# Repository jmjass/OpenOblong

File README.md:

# OpenRectangleCubsMod
Custom PCBs for a RP2040 powered rectangle controller.

Modified version of https://github.com/Armastardo/OpenRectangle that decreases size of the PCB and changes button layout to accomodate.

Original Dimensions: 339.13mm x 141.22mm

Modified Dimensions: 282.7mm x 136.22mm

Case Dimensions: 296mm x 154.4mm (~11.65" x ~6.08")

(Thickness of the case varies based on thickness of acrylic layers)

## Part Links:

Case Standoffs: 

https://www.aliexpress.us/item/2251832708378430.html?gatewayAdapt=glo2usa4itemAdapt&_randl_shipto=US

Calculate the thickness of your case and order standoffs about 1mm shorter than the case.

Case Screws: 
https://www.amazon.com/dp/B0798227SK?psc=1&ref=ppx_yo2ov_dt_b_product_details

Any M2 screws will work, I got these because I wanted black ones that are flush with the case.

Acrylic:

https://houstonacrylic.com/

There is a huge variety of colors and different designs of acrylic offered by these guys but they are a bit more expensive than other places. Also I had to pay about $17 for shipping so be sure to account for shipping costs in budget. If you order a 12 x 19 inch sheet from here you are able to cut 3 layers out of it.

If you are trying to make it as cheap as possible, I would recommend shopping around for clear acrylic because clear seemed to be the cheapest when I was looking. Here are a couple different thickness ones from amazon that I found:

1/8" For Top/Bottom Layers + PCB Layers on Aluminum Switchplate Design: https://www.amazon.com/dp/B09XR8NB28?psc=1&ref=ppx_yo2ov_dt_b_product_details

Acrylic Switchplate (.06"): https://www.amazon.com/dp/B09LTYDYKP?psc=1&ref=ppx_yo2ov_dt_b_product_details

PCB Layer/Hotswap Cutout Layer on Acylic Switchplate Design (.08"): https://www.amazon.com/dp/B09N3PN8PG?ref=ppx_yo2ov_dt_b_product_details&th=1

I recommend doing some searching on your own as there may be different options that are cheaper. 8" x 12" works the best for cutting 1 panel per sheet and for getting mroe than 1 panel per sheet you need multiples of 6.315" x 12". For example, 12" x 19" can get you 3 layers with very little margin of error or 12" x 21" would get you 3 layers way more comfortable although you are unlikely to find this size and would more commonly find 12" x 24"

3.5mm M1.6 PCB Standoffs:

https://www.ebay.com/itm/185215966272?var=692974532230

3mm M1.6 PCB Screws:

https://www.ebay.com/itm/183908369734

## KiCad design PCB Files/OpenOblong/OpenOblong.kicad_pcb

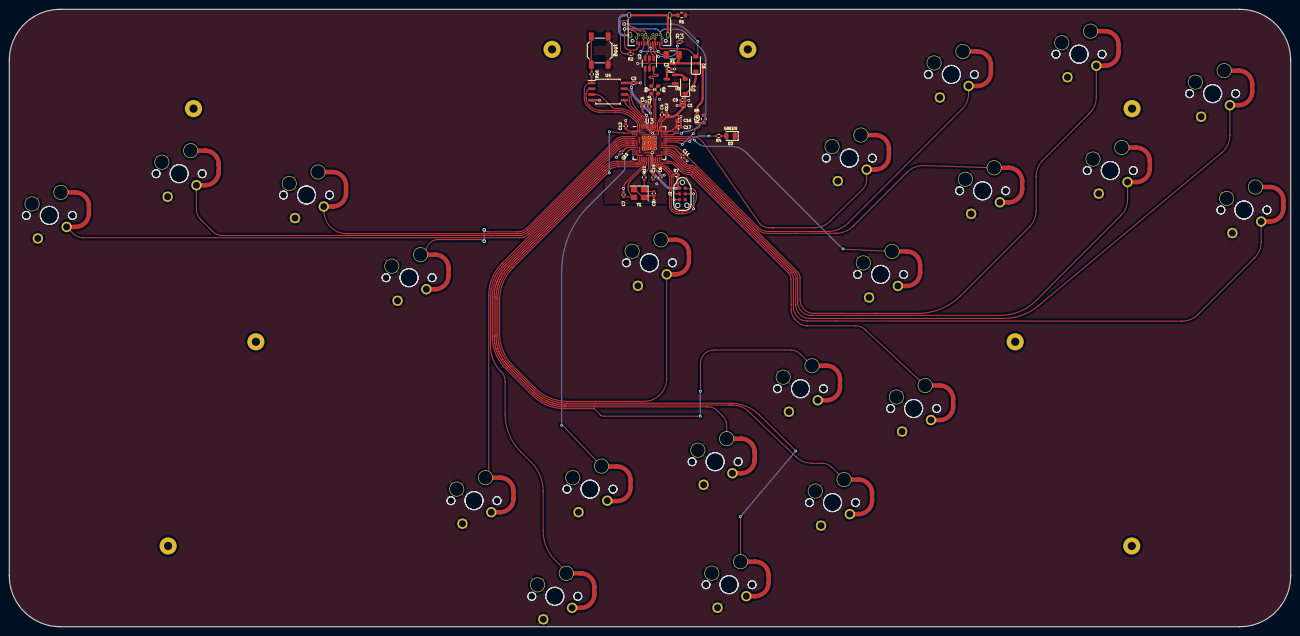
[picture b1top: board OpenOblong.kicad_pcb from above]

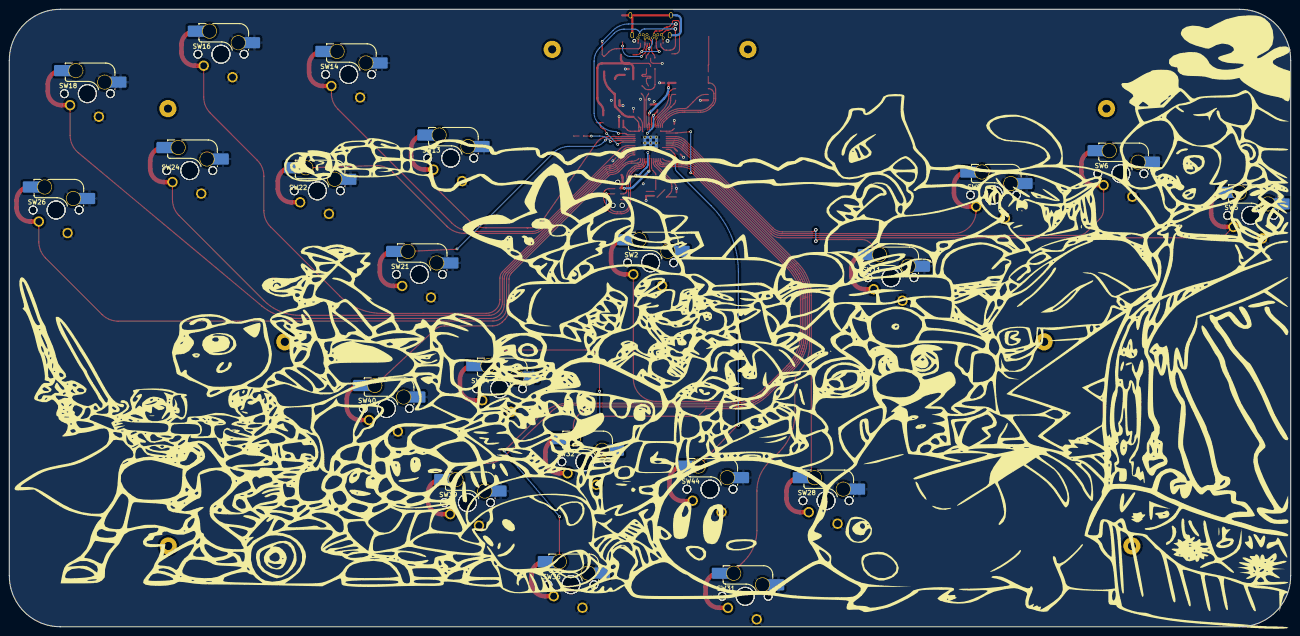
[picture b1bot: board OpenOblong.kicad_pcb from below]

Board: 2 copper layers, 282.7 x 136.2 mm, 90 parts (21 on the bottom side), 54 nets.

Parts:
C1, C2, C4, C10: 1uF; C_0402_1005Metric
C3, C5, C6, C11, C12, C13, C14, C15, C16, C17: 100nF; C_0402_1005Metric
C7, C8: 22pF; C_0402_1005Metric
C9: 10uF; C_0402_1005Metric
D1, D2: Schottky Diode; CUSTOM D_SOD-123
D3: GREEN; LED_0805_2012Metric
F1: 500 mA; Fuse_1206_3216Metric
H4, H5, H6, H7, H8, H9, H10, H11: MountingHole; MountingHole_2.2mm_M2_ISO14580_Pad
J1: USB C Connector; TYPE-C_24P_QCHT
J2: JTAG_TC2030; CON_TC2030_outlined
R1: 1M; R_0603_1608Metric
R2, R3: 5.1k; R_0402_1005Metric
R4, R7: 10k; R_0402_1005Metric
R5: 5.6k; R_0603_1608Metric
R6: 10k; R_0603_1608Metric
R8, R9: 27; R_0603_1608Metric
R10, R11: 1k; R_0402_1005Metric
SW1: Boot; SW_SPST_SKQG_WithStem
SW2, SW5, SW6, SW9, SW11, SW13, SW14, SW16, SW18, SW21, SW22, SW24, SW26, SW28, SW31, SW32, SW34, SW36, SW39, SW40, SW44: MX_SW_HS; SW_MX_HS_1u
SW3, SW4, SW7, SW8, SW10, SW12, SW15, SW17, SW19, SW20, SW23, SW25, SW27, SW29, SW30, SW33, SW35, SW37, SW38, SW41, SW45: MX_SW_solder; SW_MX_1u
U1: XC6206; SOT-23
U2: USBLC6-2SC6; SOT-23-6
U3: RP2040; RP2040-QFN-56
U4: W25Q128JVS; SOIC-8_5.23x5.23mm_P1.27mm
Y1: 12MHz; Crystal_SMD_3225-4Pin_3.2x2.5mm

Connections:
3vCable: D2.2 (A), J1.A2 (TX1+), J1.B2 (TX2+)
+1V1: C4.1, C5.1, C6.1, U3.23 (DVDD), U3.45 (VREG_VOUT), U3.50 (DVDD)
+3V3: C1.2, C3.1, C9.1, C10.1, C11.1, C12.1, C13.1, C14.1, C15.1, C16.1, C17.1, D1.1 (K), D2.1 (K), J2.1 (VCC), R7.1, U3.1 (IOVDD), U3.10 (IOVDD), U3.22 (IOVDD), U3.33 (IOVDD), U3.42 (IOVDD), U3.43 (ADC_AVDD), U3.44 (VREG_VIN), U3.48 (USB_VDD), U3.49 (IOVDD), U4.8 (VCC)
+5V: C2.2, F1.2, R5.1, U1.3 (VI), U2.5 (VBUS)
/D_+: R8.2, U3.47 (D+)
/D_-: R9.2, U3.46 (D-)
/XTAL_O: C8.2, R11.1, Y1.1
/~USB_BOOT: R10.1, SW1.2
A: SW38.1, SW39.2, U3.17 (GPIO14)
B: SW20.1, SW21.2, U3.38 (GPIO26/ADC0)
CS: R10.2, U3.56 (QSPI_SS_N), U4.1 (~CS)
C_DN: SW36.2, SW37.1, U3.18 (GPIO15)
C_LT: SW32.2, SW33.1, U3.16 (GPIO13)
C_RT: SW40.2, SW41.1, U3.27 (GPIO16)
C_UP: SW34.2, SW35.1, U3.15 (GPIO12)
D+: R8.1, U2.6 (I/O1)
D-: R9.1, U2.4 (I/O2)
DATA: J1.A11 (RX2+), J1.B11 (RX1+), U3.40 (GPIO28/ADC2)
DBUS+: J1.A6 (D+), J1.B6 (D+), U2.1 (I/O1)
DBUS-: J1.A7 (D-), J1.B7 (D-), U2.3 (I/O2)
DOWN: SW8.1, SW9.2, U3.5 (GPIO3)
GND: C1.1, C2.1, C3.2, C4.2, C5.2, C6.2, C7.1, C8.1, C9.2, C10.2, C11.2, C12.2, C13.2, C14.2, C15.2, C16.2, C17.2, D3.1 (K), J1.A1 (GND), J1.A12 (GND), J1.B1 (GND), J1.B12 (GND), J2.5 (GND), R1.1, R2.1, R3.2, R6.2, SW1.1, SW2.1, SW3.2, SW4.2, SW5.1, SW6.1, SW7.2, SW8.2, SW9.1, SW10.2, SW11.1, SW12.2, SW13.1, SW14.1, SW15.2, SW16.1, SW17.2, SW18.1, SW19.2, SW20.2, SW21.1, SW22.1, SW23.2, SW24.1, SW25.2, SW26.1, SW27.2, SW28.1, SW29.2, SW30.2, SW31.1, SW32.1, SW33.2, SW34.1, SW35.2, SW36.1, SW37.2, SW38.2, SW39.1, SW40.1, SW41.2, SW44.1, SW45.2, U1.1 (GND), U2.2 (GND), U3.19 (TESTEN), U3.57 (GND), U4.4 (GND), Y1.2, Y1.4
L: SW4.1, SW5.2, U3.7 (GPIO5)
LEFT: SW6.2, SW7.1, U3.6 (GPIO4)
LS: SW16.2, SW17.1, U3.31 (GPIO20)
M1: SW28.2, SW29.1, U3.8 (GPIO6)
M2: SW30.1, SW31.2, U3.9 (GPIO7)
M3: SW44.2, SW45.1, U3.11 (GPIO8)
MS: SW18.2, SW19.1, U3.29 (GPIO18)
unnamed: D1.2 (A), U1.2 (VO)
unnamed: D3.2 (A), R4.2
unnamed: F1.1, J1.A4 (VBUS), J1.A9 (VBUS), J1.B4 (VBUS), J1.B9 (VBUS)
unnamed: J1.A5 (CC1), R3.1
unnamed: J1.B5 (CC2), R2.2
unnamed: J1.S1 (SHIELD), R1.2
PICO_LED: R4.1, U3.37 (GPIO25)
QSPI_CLK: U3.52 (QSPI_SCLK), U4.6 (CLK)
R: SW12.1, SW13.2, U3.39 (GPIO27/ADC1)
RIGHT: SW10.1, SW11.2, U3.4 (GPIO2)
SD0: U3.53 (QSPI_SD0), U4.5 (DI(IO0))
SD1: U3.55 (QSPI_SD1), U4.2 (DO(IO1))
SD2: U3.54 (QSPI_SD2), U4.3 (IO2)
SD3: U3.51 (QSPI_SD3), U4.7 (IO3)
START: SW2.2, SW3.1, U3.2 (GPIO0)
SWCLK: J2.4 (SWCLK), U3.24 (SWCLK)
SWD: J2.2 (SWDIO), U3.25 (SWDIO)
UP: SW26.2, SW27.1, U3.28 (GPIO17)
VBUS_SENSE: R5.2, R6.1, U3.36 (GPIO24)
X: SW22.2, SW23.1, U3.32 (GPIO21)
XTAL_IN: C7.2, U3.20 (XTAL_IN), Y1.3
XTAL_OUT: R11.2, U3.21 (XTAL_OUT)
Y: SW14.2, SW15.1, U3.34 (GPIO22)
Z: SW24.2, SW25.1, U3.30 (GPIO19)
~RESET: J2.3 (~RST), R7.2, U3.26 (~RUN)

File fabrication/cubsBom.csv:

Comment,Designator,Footprint,LCSC
1uF,"C1,C2,C4,C10",Capacitor_SMD:C_0402_1005Metric,C52923
100nF,"C3,C5,C6,C11,C12,C13,C14,C15,C16,C17",Capacitor_SMD:C_0402_1005Metric,C1525
10uF,C9,Capacitor_SMD:C_0402_1005Metric,C15525
22pF,"C7,C8",Capacitor_SMD:C_0402_1005Metric,C1555
Schottky Diode,"D1,D2",qw-footprints:CUSTOM D_SOD-123,C130880
Fuse_Small,F1,Fuse:Fuse_1206_3216Metric,C70069
USB C Connector,J1,qw-footprints:TYPE-C_24P_QCHT,C456013
1M,R1,Resistor_SMD:R_0603_1608Metric,C22935
5.1k,"R2,R3",Resistor_SMD:R_0402_1005Metric,C26000
470,R4,Resistor_SMD:R_0402_1005Metric,C25167
5.6k,R5,Resistor_SMD:R_0603_1608Metric,C23189
27,"R8,R9",Resistor_SMD:R_0603_1608Metric,C25190
1k,"R10,R11",Resistor_SMD:R_0402_1005Metric,C11702
Boot,SW1,Button_Switch_SMD:SW_SPST_SKQG_WithStem,C202424
XC6206,U1,Package_TO_SOT_SMD:SOT-23,C5446
USBLC6-2SC6,U2,Package_TO_SOT_SMD:SOT-23-6,C5261088
RP2040,U3,qw-footprints:RP2040-QFN-56,C2040
W25Q128JVS,U4,Package_SO:SOIC-8_5.23x5.23mm_P1.27mm,C97521
12MHz,Y1,Crystal:Crystal_SMD_3225-4Pin_3.2x2.5mm,C9002
PICO_LED,D3,LED_SMD:LED_0805_2012Metric,C84260

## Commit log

2023-03-15 modified OpenRectangle design
    Modified OpenRectangle design to make it smaller and change button positions
2023-03-15 updated case folders
2023-03-15 updated case diagram
2023-03-15 fixed pcb layer thickness
2023-03-16 updated mounting hole size
2023-03-16 edited case and added annotations to expanded
2023-03-16 updated fabrication files
2023-03-17 updated case
2023-03-17 generated new gerbers
2023-03-17 updated BOM
2023-03-18 updated case to make PCB layer walls bigger
2023-03-22 edited case and added laser cut files
2023-03-23 added picture of alternate case version
2023-03-23 updated case holes to fit aliexpress standoffs
2023-03-23 updated laser printing files
2023-04-12 revamped case
2023-04-20 Added optional buttons
2023-05-22 updated pinout to default haybox and revised case
2023-05-26 updated casse
2023-06-21 added BottomPCBLayer
2023-07-22 updated board and case
2023-08-11 changed c-up wiring
